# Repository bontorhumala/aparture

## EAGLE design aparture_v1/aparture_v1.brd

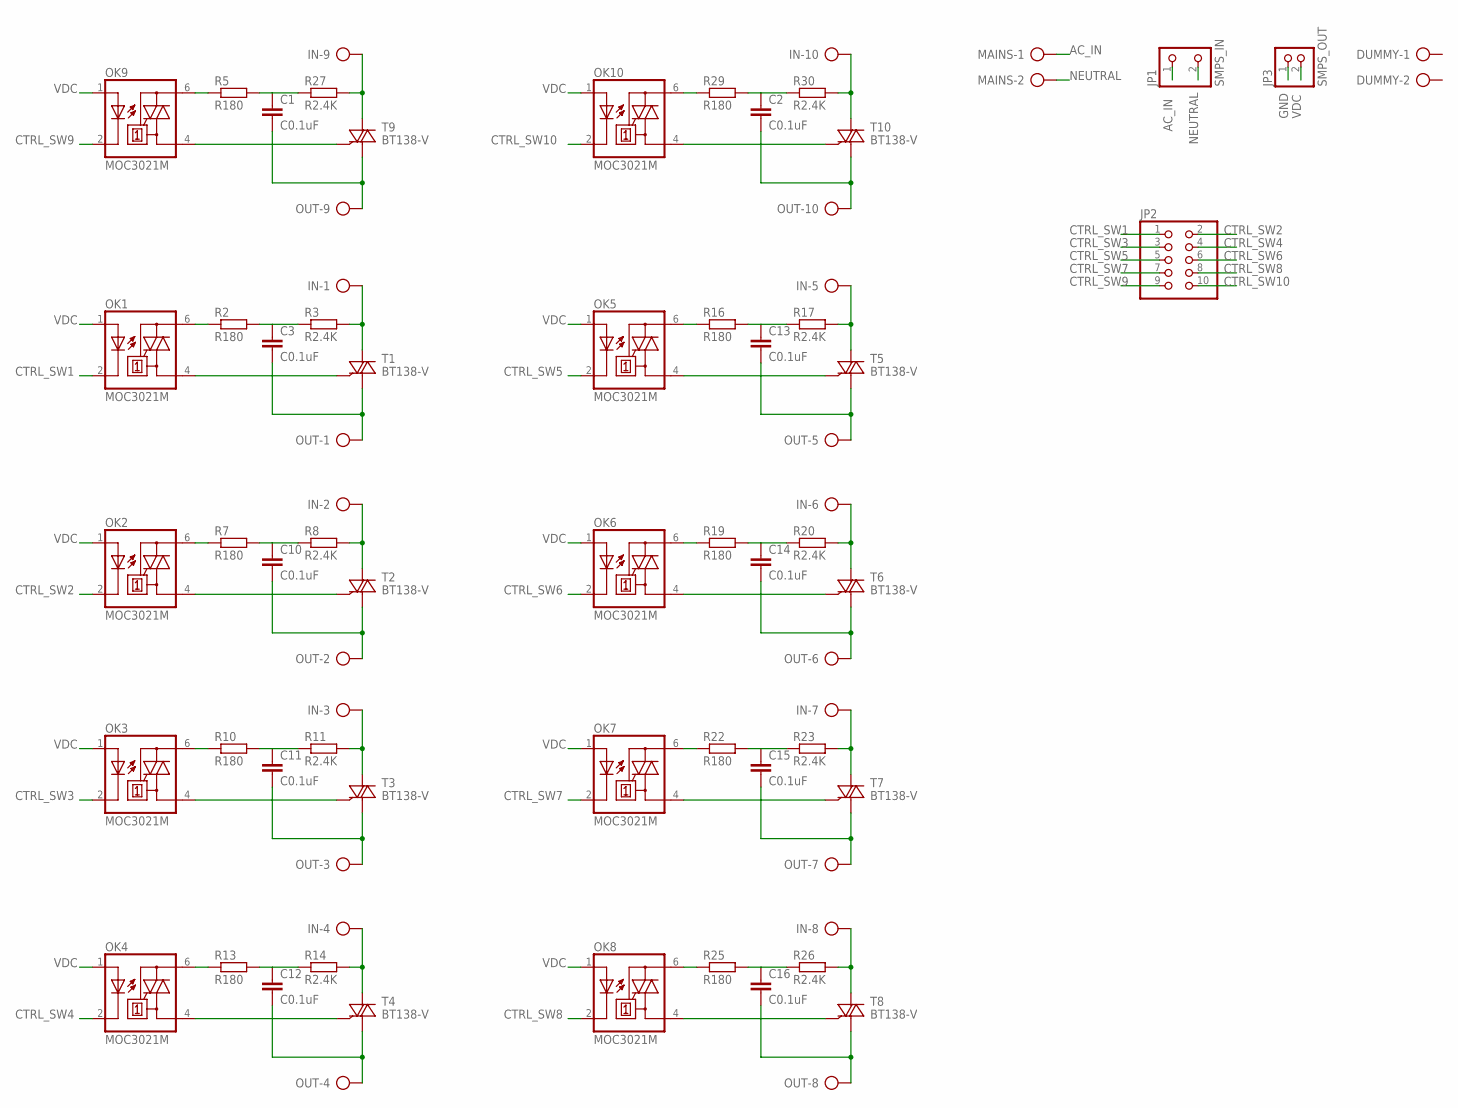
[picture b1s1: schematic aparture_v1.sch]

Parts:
C1, C2, C3, C10, C11, C12, C13, C14, C15, C16: C0.1uF; C0805
DUMMY: AK300/2
IN: AK300/10
JP1: SMPS_IN
JP2: PINHD-2X5; 2X05
JP3: SMPS_OUT; 1X02
MAINS: AK300/2
OK1, OK2, OK3, OK4, OK5, OK6, OK7, OK8, OK9, OK10: MOC3021M; DIL06
OUT: AK300/10
R2, R5, R7, R10, R13, R16, R19, R22, R25, R29: R180; M0805
R3, R8, R11, R14, R17, R20, R23, R26, R27, R30: R2.4K; M0805
T1, T2, T3, T4, T5, T6, T7, T8, T9, T10: BT138-V; TO220BV

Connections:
AC_IN: JP1.1, MAINS.1
CTRL_SW1: JP2.1, OK1.2 (C)
CTRL_SW2: JP2.2, OK2.2 (C)
CTRL_SW3: JP2.3, OK3.2 (C)
CTRL_SW4: JP2.4, OK4.2 (C)
CTRL_SW5: JP2.5, OK5.2 (C)
CTRL_SW6: JP2.6, OK6.2 (C)
CTRL_SW7: JP2.7, OK7.2 (C)
CTRL_SW8: JP2.8, OK8.2 (C)
CTRL_SW9: JP2.9, OK9.2 (C)
CTRL_SW10: JP2.10, OK10.2 (C)
GND: JP3.1
unnamed: OK1.6 (A2), R2.1
unnamed: C3.1, R2.2, R3.1
unnamed: OK1.4 (A1), T1.G
unnamed: C3.2, OUT.1, T1.T1 (A1)
unnamed: IN.1, R3.2, T1.T2 (A2)
unnamed: OK2.6 (A2), R7.1
unnamed: C10.1, R7.2, R8.1
unnamed: OK2.4 (A1), T2.G
unnamed: C10.2, OUT.2, T2.T1 (A1)
unnamed: OK3.6 (A2), R10.1
unnamed: C11.1, R10.2, R11.1
unnamed: OK3.4 (A1), T3.G
unnamed: C11.2, OUT.3, T3.T1 (A1)
unnamed: OK4.6 (A2), R13.1
unnamed: C12.1, R13.2, R14.1
unnamed: OK4.4 (A1), T4.G
unnamed: C12.2, OUT.4, T4.T1 (A1)
unnamed: OK5.6 (A2), R16.1
unnamed: C13.1, R16.2, R17.1
unnamed: OK5.4 (A1), T5.G
unnamed: C13.2, OUT.5, T5.T1 (A1)
unnamed: OK6.6 (A2), R19.1
unnamed: C14.1, R19.2, R20.1
unnamed: OK6.4 (A1), T6.G
unnamed: C14.2, OUT.6, T6.T1 (A1)
unnamed: OK7.6 (A2), R22.1
unnamed: C15.1, R22.2, R23.1
unnamed: OK7.4 (A1), T7.G
unnamed: C15.2, OUT.7, T7.T1 (A1)
unnamed: OK8.6 (A2), R25.1
unnamed: C16.1, R25.2, R26.1
unnamed: OK8.4 (A1), T8.G
unnamed: C16.2, OUT.8, T8.T1 (A1)
unnamed: IN.2, R8.2, T2.T2 (A2)
unnamed: IN.3, R11.2, T3.T2 (A2)
unnamed: IN.4, R14.2, T4.T2 (A2)
unnamed: IN.8, R26.2, T8.T2 (A2)
unnamed: IN.7, R23.2, T7.T2 (A2)
unnamed: IN.6, R20.2, T6.T2 (A2)
unnamed: IN.5, R17.2, T5.T2 (A2)
unnamed: OK9.6 (A2), R5.1
unnamed: C1.1, R5.2, R27.1
unnamed: OK9.4 (A1), T9.G
unnamed: C1.2, OUT.9, T9.T1 (A1)
unnamed: OK10.6 (A2), R29.1
unnamed: C2.1, R29.2, R30.1
unnamed: OK10.4 (A1), T10.G
unnamed: C2.2, OUT.10, T10.T1 (A1)
unnamed: IN.9, R27.2, T9.T2 (A2)
unnamed: IN.10, R30.2, T10.T2 (A2)
NEUTRAL: JP1.2, MAINS.2
VDC: JP3.2, OK1.1 (A), OK2.1 (A), OK3.1 (A), OK4.1 (A), OK5.1 (A), OK6.1 (A), OK7.1 (A), OK8.1 (A), OK9.1 (A), OK10.1 (A)

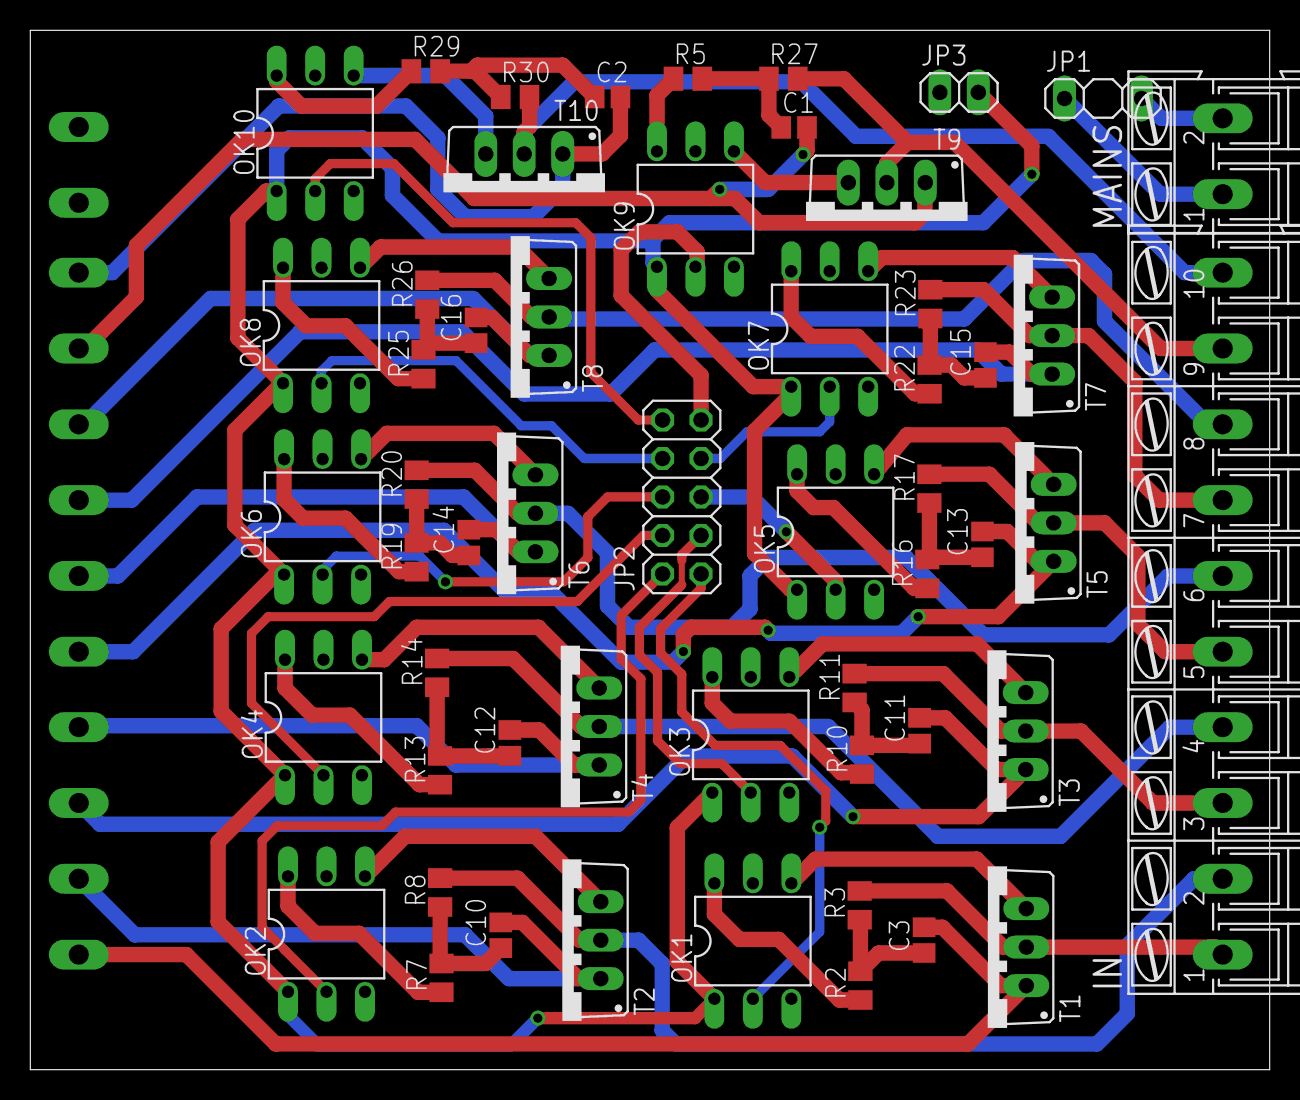
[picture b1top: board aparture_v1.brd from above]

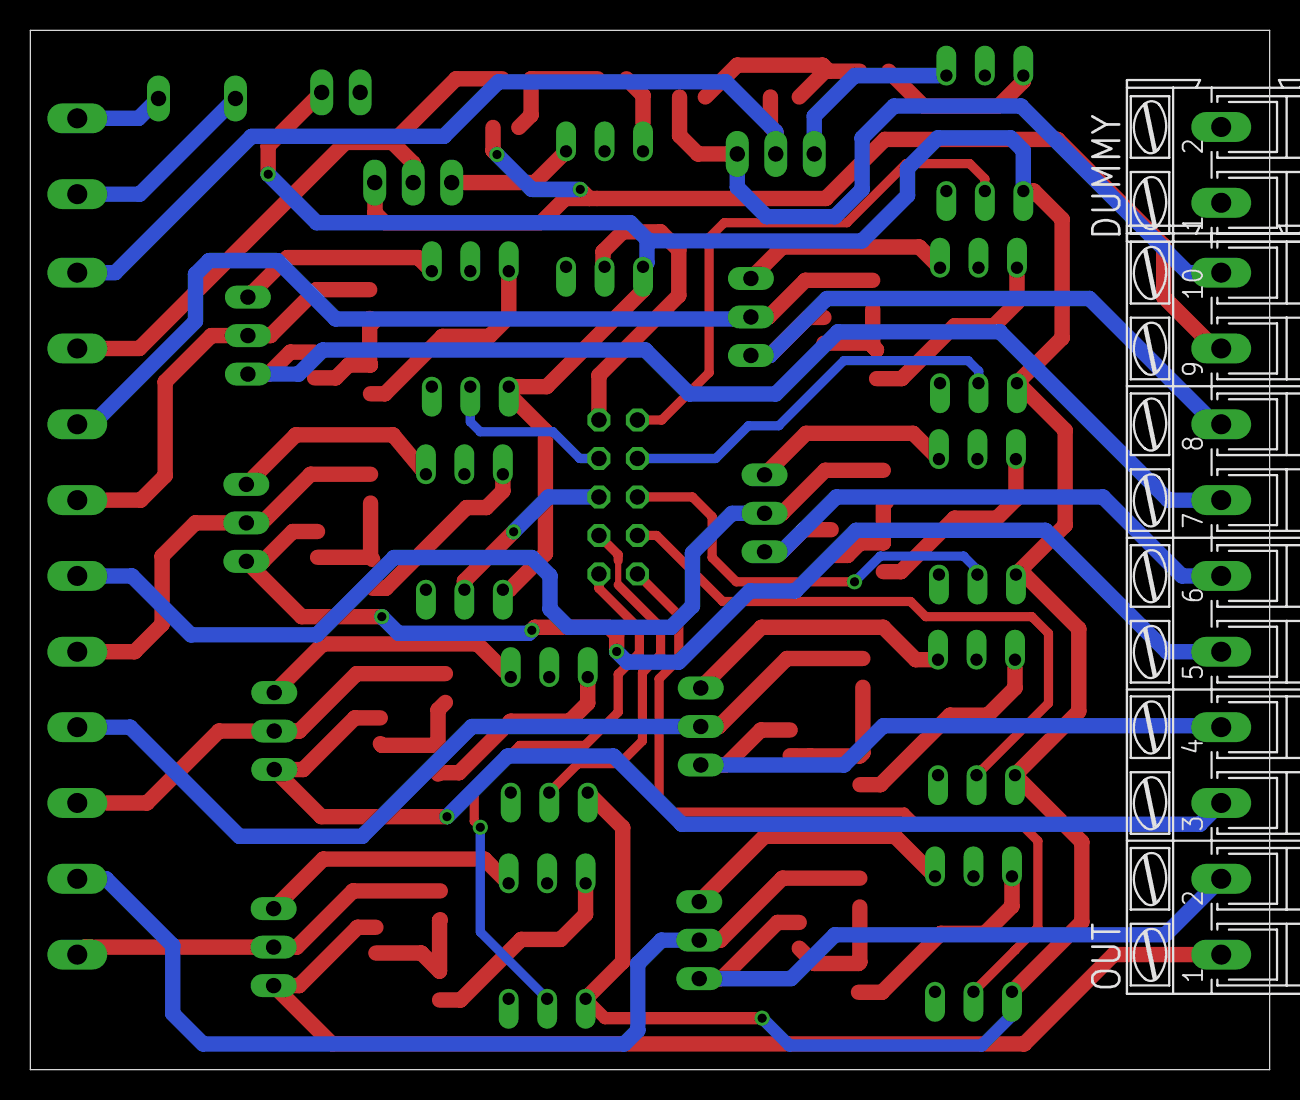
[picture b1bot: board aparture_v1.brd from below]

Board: 2 copper layers, 81.8 x 68.6 mm, 57 parts (2 on the bottom side), 63 nets.

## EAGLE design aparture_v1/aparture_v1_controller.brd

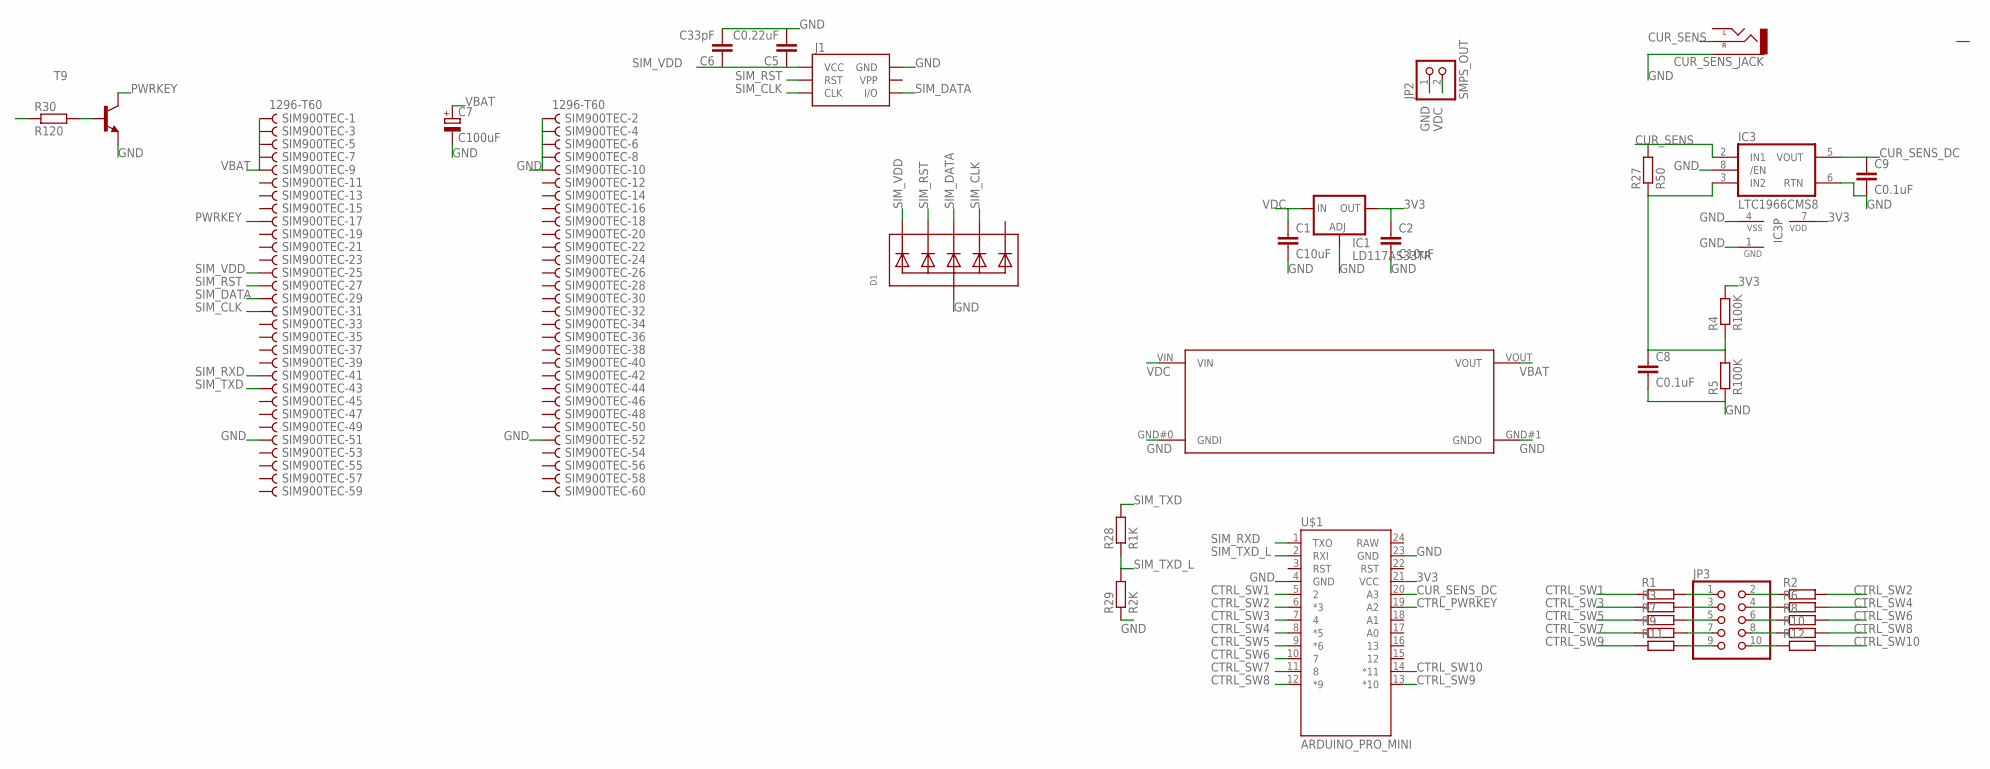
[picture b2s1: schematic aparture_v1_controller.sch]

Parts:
C1, C2: C10uF; C0805
C5: C0.22uF; C0805
C6: C33pF; C0805
C7: C100uF; 153CLV-0605
C8, C9: C0.1uF; C0805
CUR_SENS_JACK: AUDIO-JACKSMD2; AUDIO-JACK-3.5MM-SMD
D1: TVSARRAY_5LANE; SOT363
IC1: LD117AS33TR; SOT223
IC3: LTC1966CMS8; MSOP8
J1: SIMHOLDERSIM; SIMHOLDER
JP2: SMPS_OUT; 1X02
JP3: PINHD-2X5; 2X05
R1, R2, R3, R6, R7, R8, R9, R10, R11, R12: R-EU_R0603; R0603
R4, R5: R100K; M0805
R27: R50; M0805
R28: R1K; M0805
R29: R2K; M0805
R30: R120; M0805
SIM900TEC: 1296-T60; 1296-60
T9: MMBT2222ALT1-NPN-SOT23-BEC; SOT23-BEC
U$1: ARDUINO_PRO_MINI
VOL_REG_SIM900: DCDCMODULE

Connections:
3V3: C2.1, IC1.4 (OUT), IC3.7 (VDD), R4.2, U$1.21 (VCC)
CTRL_PWRKEY: R30.1, U$1.19 (A2)
CTRL_SW1: R1.1, U$1.5 (2)
CTRL_SW2: R2.2, U$1.6 (*3)
CTRL_SW3: R3.1, U$1.7 (4)
CTRL_SW4: R6.2, U$1.8 (*5)
CTRL_SW5: R7.1, U$1.9 (*6)
CTRL_SW6: R8.2, U$1.10 (7)
CTRL_SW7: R9.1, U$1.11 (8)
CTRL_SW8: R10.2, U$1.12 (*9)
CTRL_SW9: R11.1, U$1.13 (*10)
CTRL_SW10: R12.2, U$1.14 (*11)
CUR_SENS: CUR_SENS_JACK.RING (RIGHT), IC3.2 (IN1), R27.2
CUR_SENS_DC: C9.1, IC3.5 (VOUT), U$1.20 (A3)
GND: C1.2, C2.2, C5.2, C6.2, C7.-, C8.2, C9.2, CUR_SENS_JACK.SLEEVE, D1.2 (A), IC1.1 (ADJ), IC3.1 (GND), IC3.4 (VSS), IC3.6 (RTN), IC3.8 (/EN), J1.C5 (GND), JP2.1, R5.1, R29.1, SIM900TEC.2, SIM900TEC.4, SIM900TEC.6, SIM900TEC.8, SIM900TEC.10, SIM900TEC.51, SIM900TEC.52, T9.E, U$1.4 (GND), U$1.23 (GND), VOL_REG_SIM900.GND#0 (GNDI), VOL_REG_SIM900.GND#1 (GNDO)
unnamed: JP3.1, R1.2
unnamed: JP3.3, R3.2
unnamed: JP3.5, R7.2
unnamed: JP3.7, R9.2
unnamed: JP3.9, R11.2
unnamed: JP3.2, R2.1
unnamed: C8.1, IC3.3 (IN2), R4.1, R5.2, R27.1
unnamed: R30.2, T9.B
unnamed: JP3.4, R6.1
unnamed: JP3.6, R8.1
unnamed: JP3.8, R10.1
unnamed: JP3.10, R12.1
PWRKEY: SIM900TEC.17, T9.C
SIM_CLK: D1.5 (C4), J1.C3 (CLK), SIM900TEC.31
SIM_DATA: D1.4 (C3), J1.C7 (I/O), SIM900TEC.29
SIM_RST: D1.3 (C2), J1.C2 (RST), SIM900TEC.27
SIM_RXD: SIM900TEC.41, U$1.1 (TXO)
SIM_TXD: R28.2, SIM900TEC.43
SIM_TXD_L: R28.1, R29.2, U$1.2 (RXI)
SIM_VDD: C5.1, C6.1, D1.1 (C1), J1.C1 (VCC), SIM900TEC.25
VBAT: C7.+, SIM900TEC.1, SIM900TEC.3, SIM900TEC.5, SIM900TEC.7, SIM900TEC.9, VOL_REG_SIM900.VOUT
VDC: C1.1, IC1.3 (IN), JP2.2, VOL_REG_SIM900.VIN

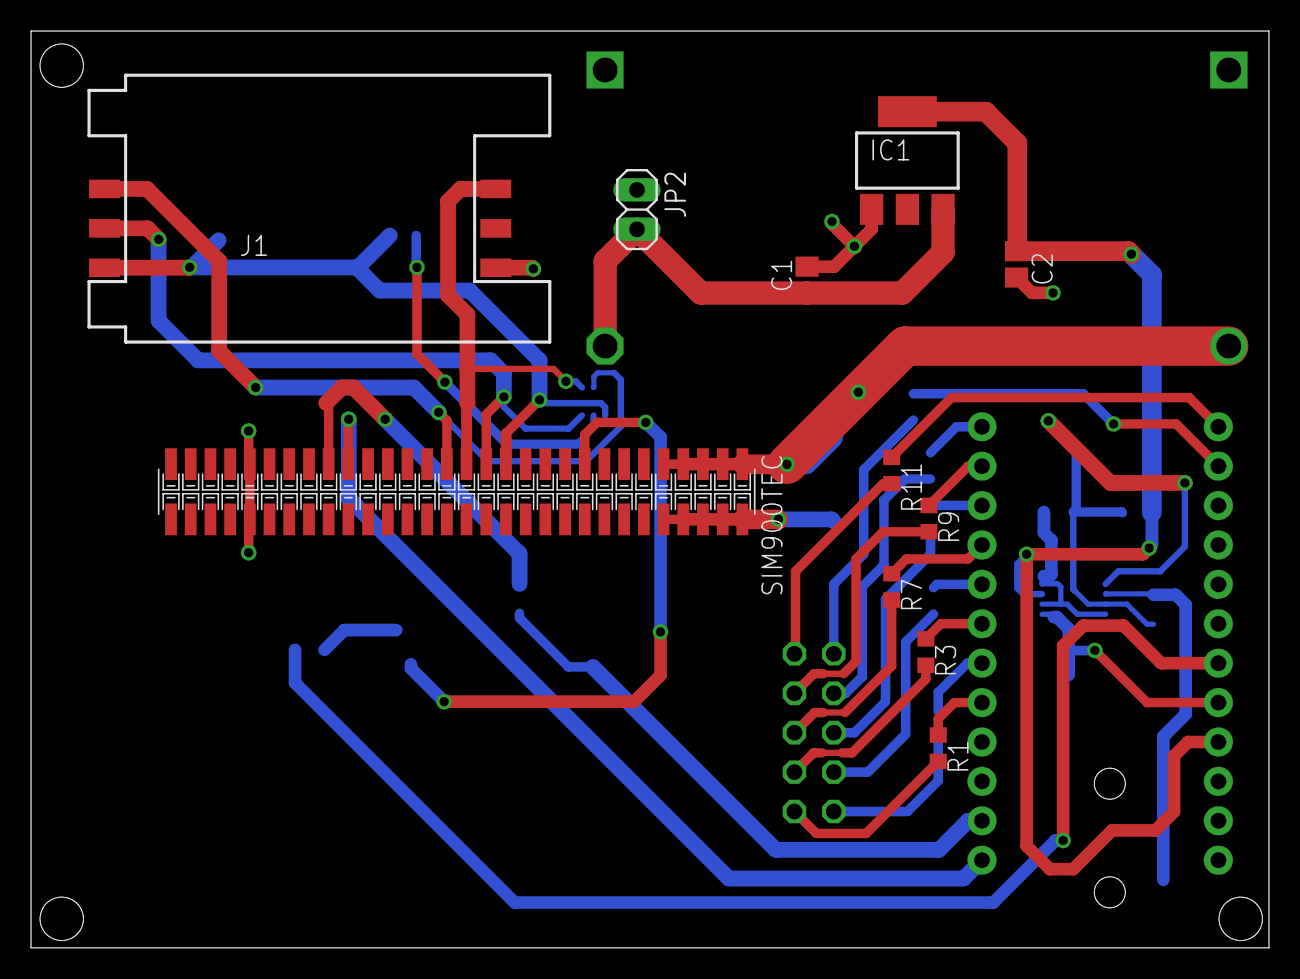
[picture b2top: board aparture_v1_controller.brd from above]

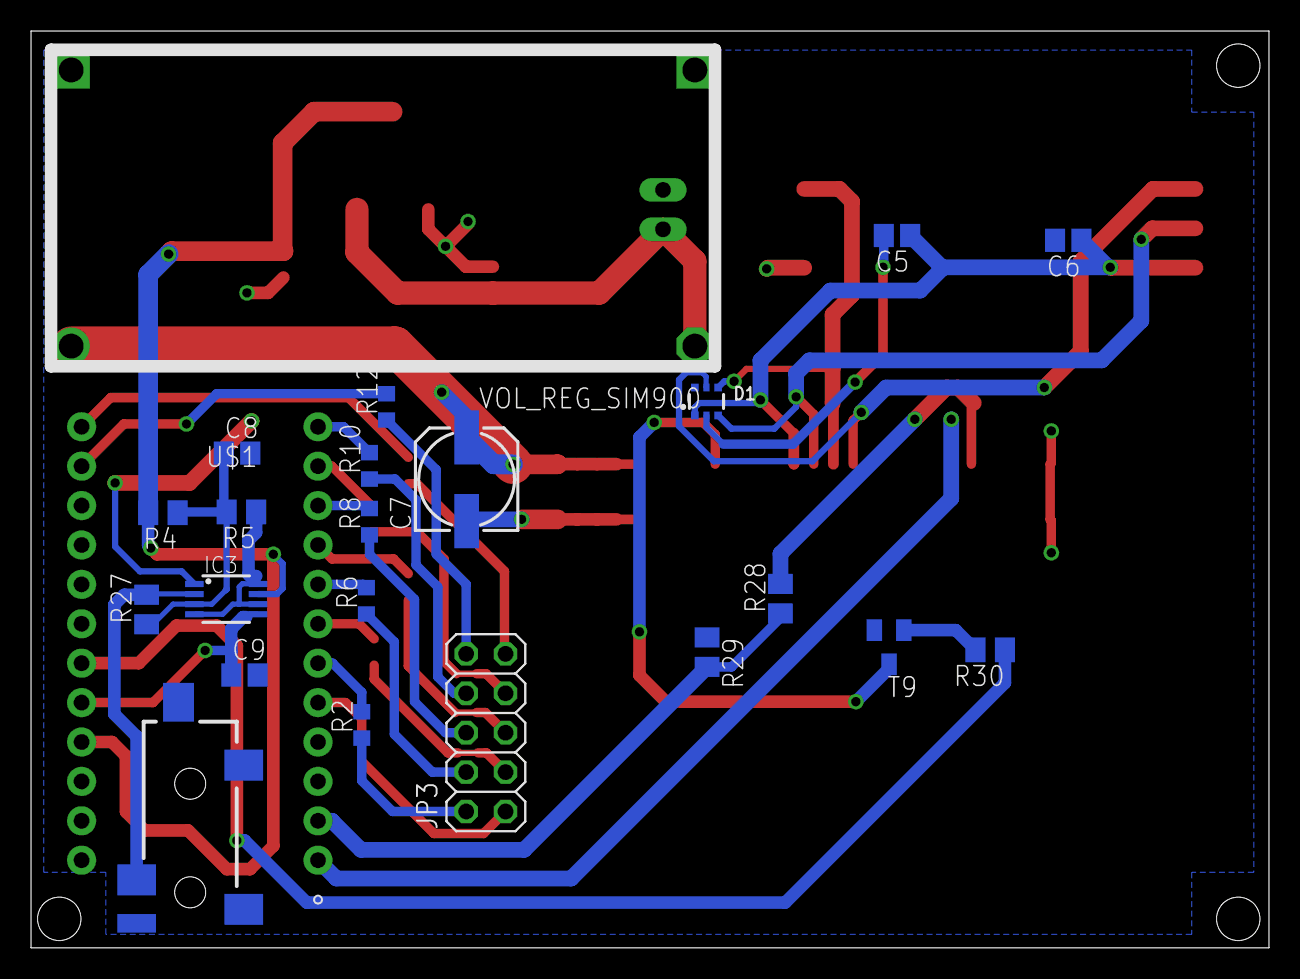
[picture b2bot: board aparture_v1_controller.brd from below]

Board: 2 copper layers, 79.8 x 59.1 mm, 34 parts (23 on the bottom side), 37 nets.

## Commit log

2014-10-14 brd and sch made for 80*70mm boards, separated controller and triacs
2014-10-14 resize boards
2014-10-14 resize to 68 mm

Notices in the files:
parts and their libraries:
SparkFun-Connectors: Licensing: Creative Commons ShareAlike 4.0 International - https://creativecommons.org/licenses/by-sa/4.0
microbuilder: This work is placed in the public domain, and may be freely used for commercial and non-commercial work with the following conditions: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
